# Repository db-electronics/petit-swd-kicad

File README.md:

# Petit SWD
Petit SWD is an ARM JTAG adapter which reduces the 2x10 100mil connector to a 1x4 100mil connector better suited for SWD debugging. It also has a type B USB input to provide power to the target board from either VBUS 5V or 3.3V from an onboard voltage regulator. This is selectable via pin header.

# Support Open Source
If you're going to use my free projects please consider sponsoring my work. Thanks!

- [Github Sponsor](https://github.com/sponsors/db-electronics)
- [Pateron](https://patreon.com/dbelectronics)

## Changelog
- [v1.0](https://github.com/db-electronics/petit-swd-kicad/releases/tag/v1.0)
  - initial release

# Copyright and Disclaimer
Copyright: René Richard

This documentation describes Open Hardware and is licensed under the
CERN OHL v. 1.2.

You may redistribute and modify this documentation under the terms of the
CERN OHL v.1.2. (http://ohwr.org/cernohl). This documentation is distributed
WITHOUT ANY EXPRESS OR IMPLIED WARRANTY, INCLUDING OF
MERCHANTABILITY, SATISFACTORY QUALITY AND FITNESS FOR A
PARTICULAR PURPOSE. Please see the CERN OHL v.1.2 for applicable
conditions

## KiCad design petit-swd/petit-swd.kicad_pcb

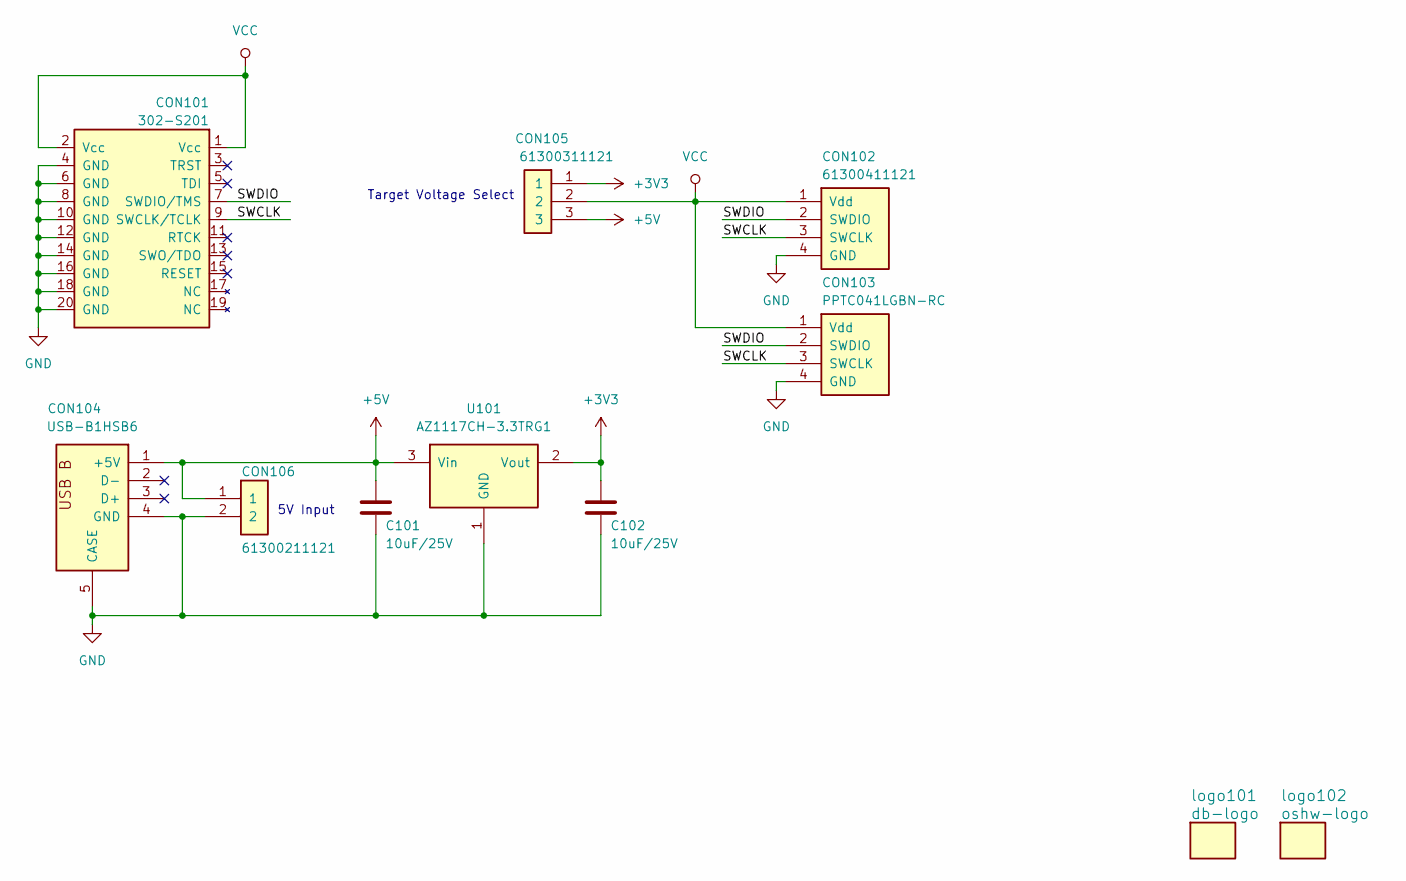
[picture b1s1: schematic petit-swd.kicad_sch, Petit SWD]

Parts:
C101, C102: 10uF/25V; 0805
CON101: 302-S201; HDR2X10-JTAG-SHROUD
CON102: 61300411121; HDR1X4
CON103: PPTC041LGBN-RC; RCP1X4_RA
CON104: USB-B1HSB6; USB-B1HSxx
CON105: 61300311121; HDR1X3
CON106: 61300211121; HDR1X2
U101: AZ1117CH-3.3TRG1; SOT-223
logo101: db-logo; db-logo_10mm
logo102: oshw-logo; oshw-logo_7.5mm

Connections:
+3V3: C102.1, CON105.1, U101.2 (Vout)
+5V: C101.1, CON104.1 (+5V), CON105.3, CON106.1, U101.3 (Vin)
/SWCLK: CON101.9 (SWCLK/TCLK), CON102.3 (SWCLK), CON103.3 (SWCLK)
/SWDIO: CON101.7 (SWDIO/TMS), CON102.2 (SWDIO), CON103.2 (SWDIO)
GND: C101.2, C102.2, CON101.4 (GND), CON101.6 (GND), CON101.8 (GND), CON101.10 (GND), CON101.12 (GND), CON101.14 (GND), CON101.16 (GND), CON101.18 (GND), CON101.20 (GND), CON102.4 (GND), CON103.4 (GND), CON104.4 (GND), CON104.5 (CASE), CON106.2, U101.1 (GND)
VCC: CON101.1 (Vcc), CON101.2 (Vcc), CON102.1 (Vdd), CON103.1 (Vdd), CON105.2

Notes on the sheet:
Target Voltage Select
5V Input

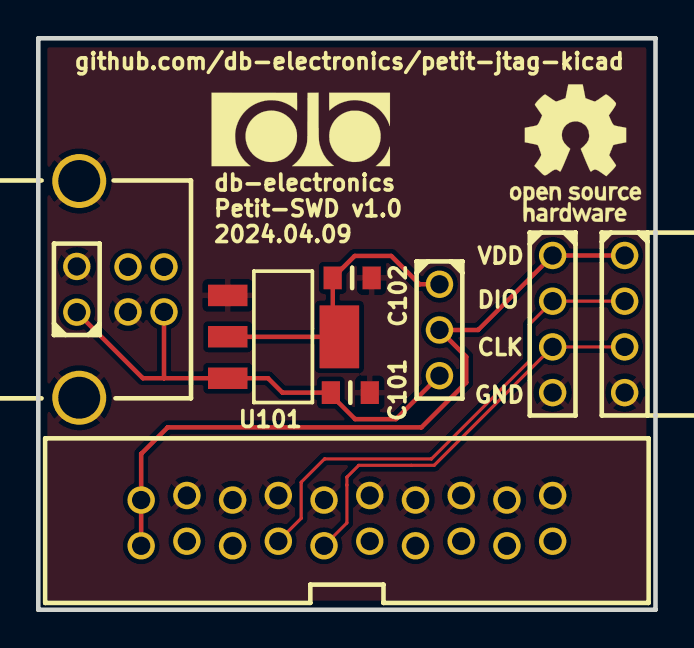
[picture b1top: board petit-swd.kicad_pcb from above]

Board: 2 copper layers, 34.3 x 31.8 mm, 11 parts (0 on the bottom side), 6 nets.

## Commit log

2024-04-10 initial commit after split from petit-jtag
2024-04-10 v1.0 files ready

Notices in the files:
petit-swd/petit-swd.kicad_pcb:
Licensed Under CERN OHL v.1.2
Copyright 2024 René Richard
